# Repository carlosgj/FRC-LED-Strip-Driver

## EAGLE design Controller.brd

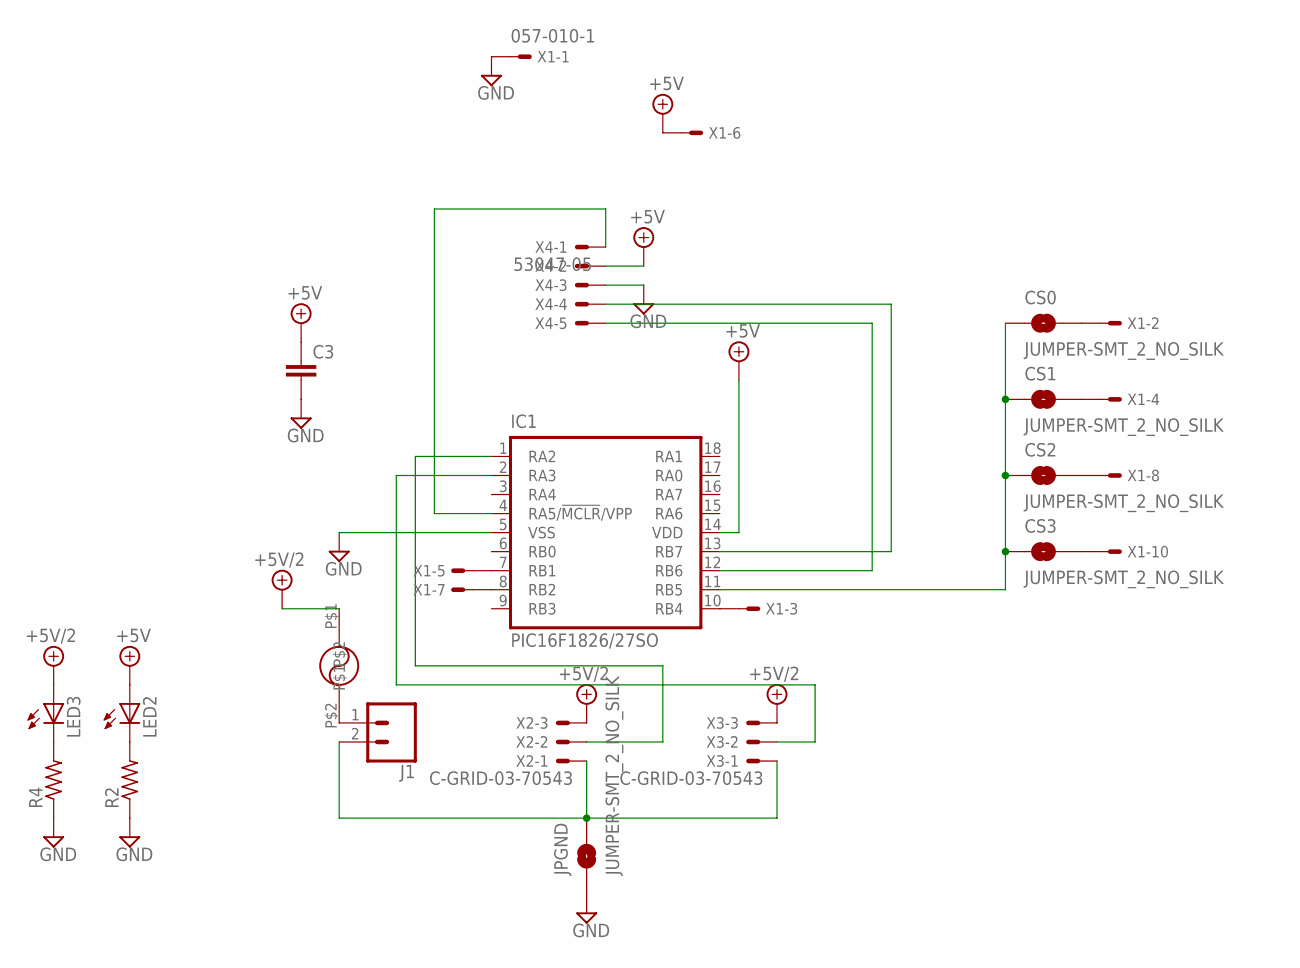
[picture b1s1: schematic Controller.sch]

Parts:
C3: C-EUC1206; C1206
CS0, CS1, CS2, CS3: JUMPER-SMT_2_NO_SILK; SMT-JUMPER_2_NO_SILK
IC1: PIC16F1826/27SO; SO-18W
J1: CONN_023.5MM; SCREWTERMINAL-3.5MM-2
JPGND: JUMPER-SMT_2_NO_SILK; SMT-JUMPER_2_NO_SILK
LED2, LED3: LEDCHIPLED_1206; CHIPLED_1206
R2, R4: R-US_R1206; R1206
U$3: 0034.6081; MSF250
X1: 057-010-1
X2, X3: C-GRID-03-70543; 70543-03
X4: 53047-05

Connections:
+5V: C3.1, IC1.14 (VDD), LED2.A, X1.6, X4.2
+5V/2: LED3.A, U$3.P$1, X2.3, X3.3
GND: C3.2, IC1.5 (VSS), JPGND.1, R2.1, R4.1, X1.1, X4.3
unnamed: IC1.10 (RB4), X1.3
unnamed: IC1.7 (RB1), X1.5
unnamed: IC1.8 (RB2), X1.7
unnamed: CS0.1, CS1.1, CS2.1, CS3.1, IC1.11 (RB5)
unnamed: CS0.2, X1.2
unnamed: CS1.2, X1.4
unnamed: CS2.2, X1.8
unnamed: CS3.2, X1.10
unnamed: J1.1, U$3.P$2
unnamed: LED3.C, R4.2
unnamed: J1.2, JPGND.2, X2.1, X3.1
unnamed: IC1.1 (RA2), X2.2
unnamed: IC1.2 (RA3), X3.2
unnamed: IC1.4 (RA5/!MCLR!/VPP), X4.1
unnamed: IC1.13 (RB7), X4.4
unnamed: IC1.12 (RB6), X4.5
unnamed: LED2.C, R2.2

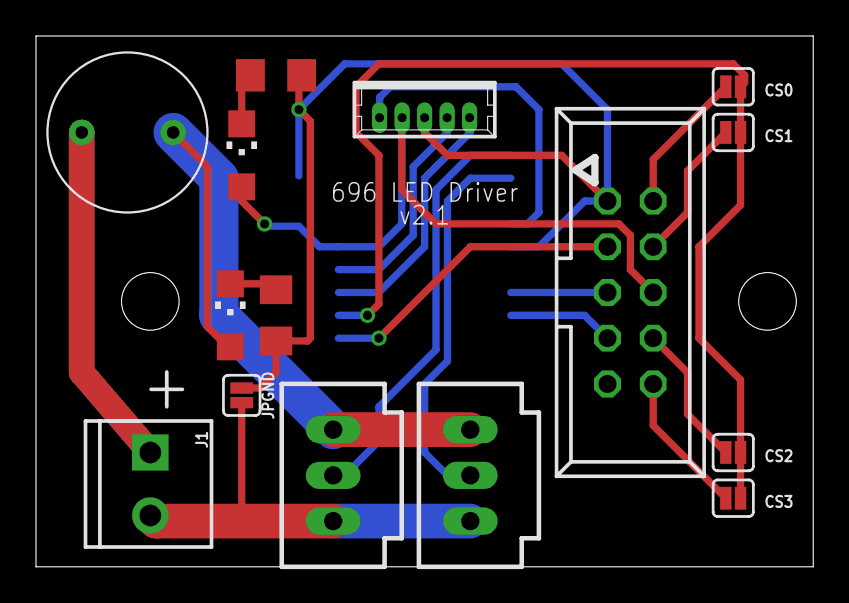
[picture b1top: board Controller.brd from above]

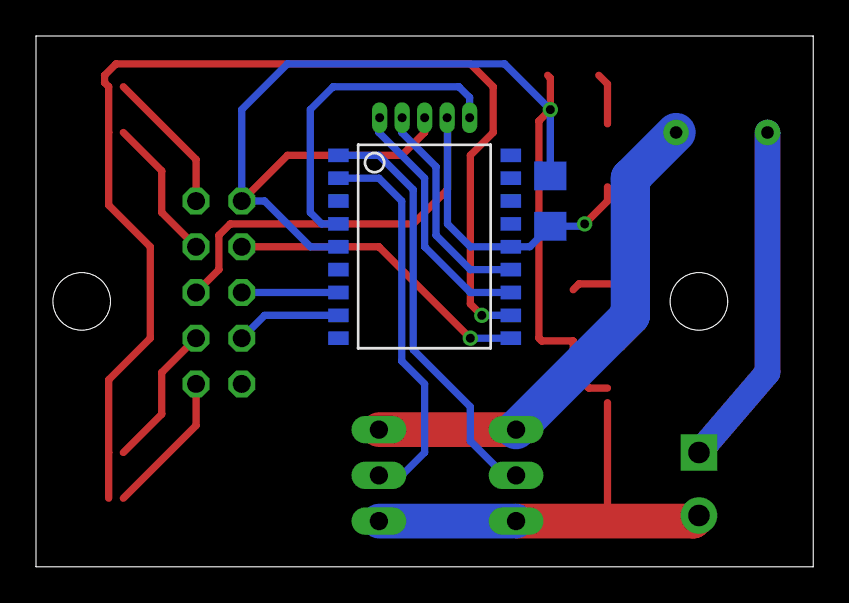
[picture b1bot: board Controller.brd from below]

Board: 2 copper layers, 43.2 x 29.5 mm, 17 parts (2 on the bottom side), 20 nets.

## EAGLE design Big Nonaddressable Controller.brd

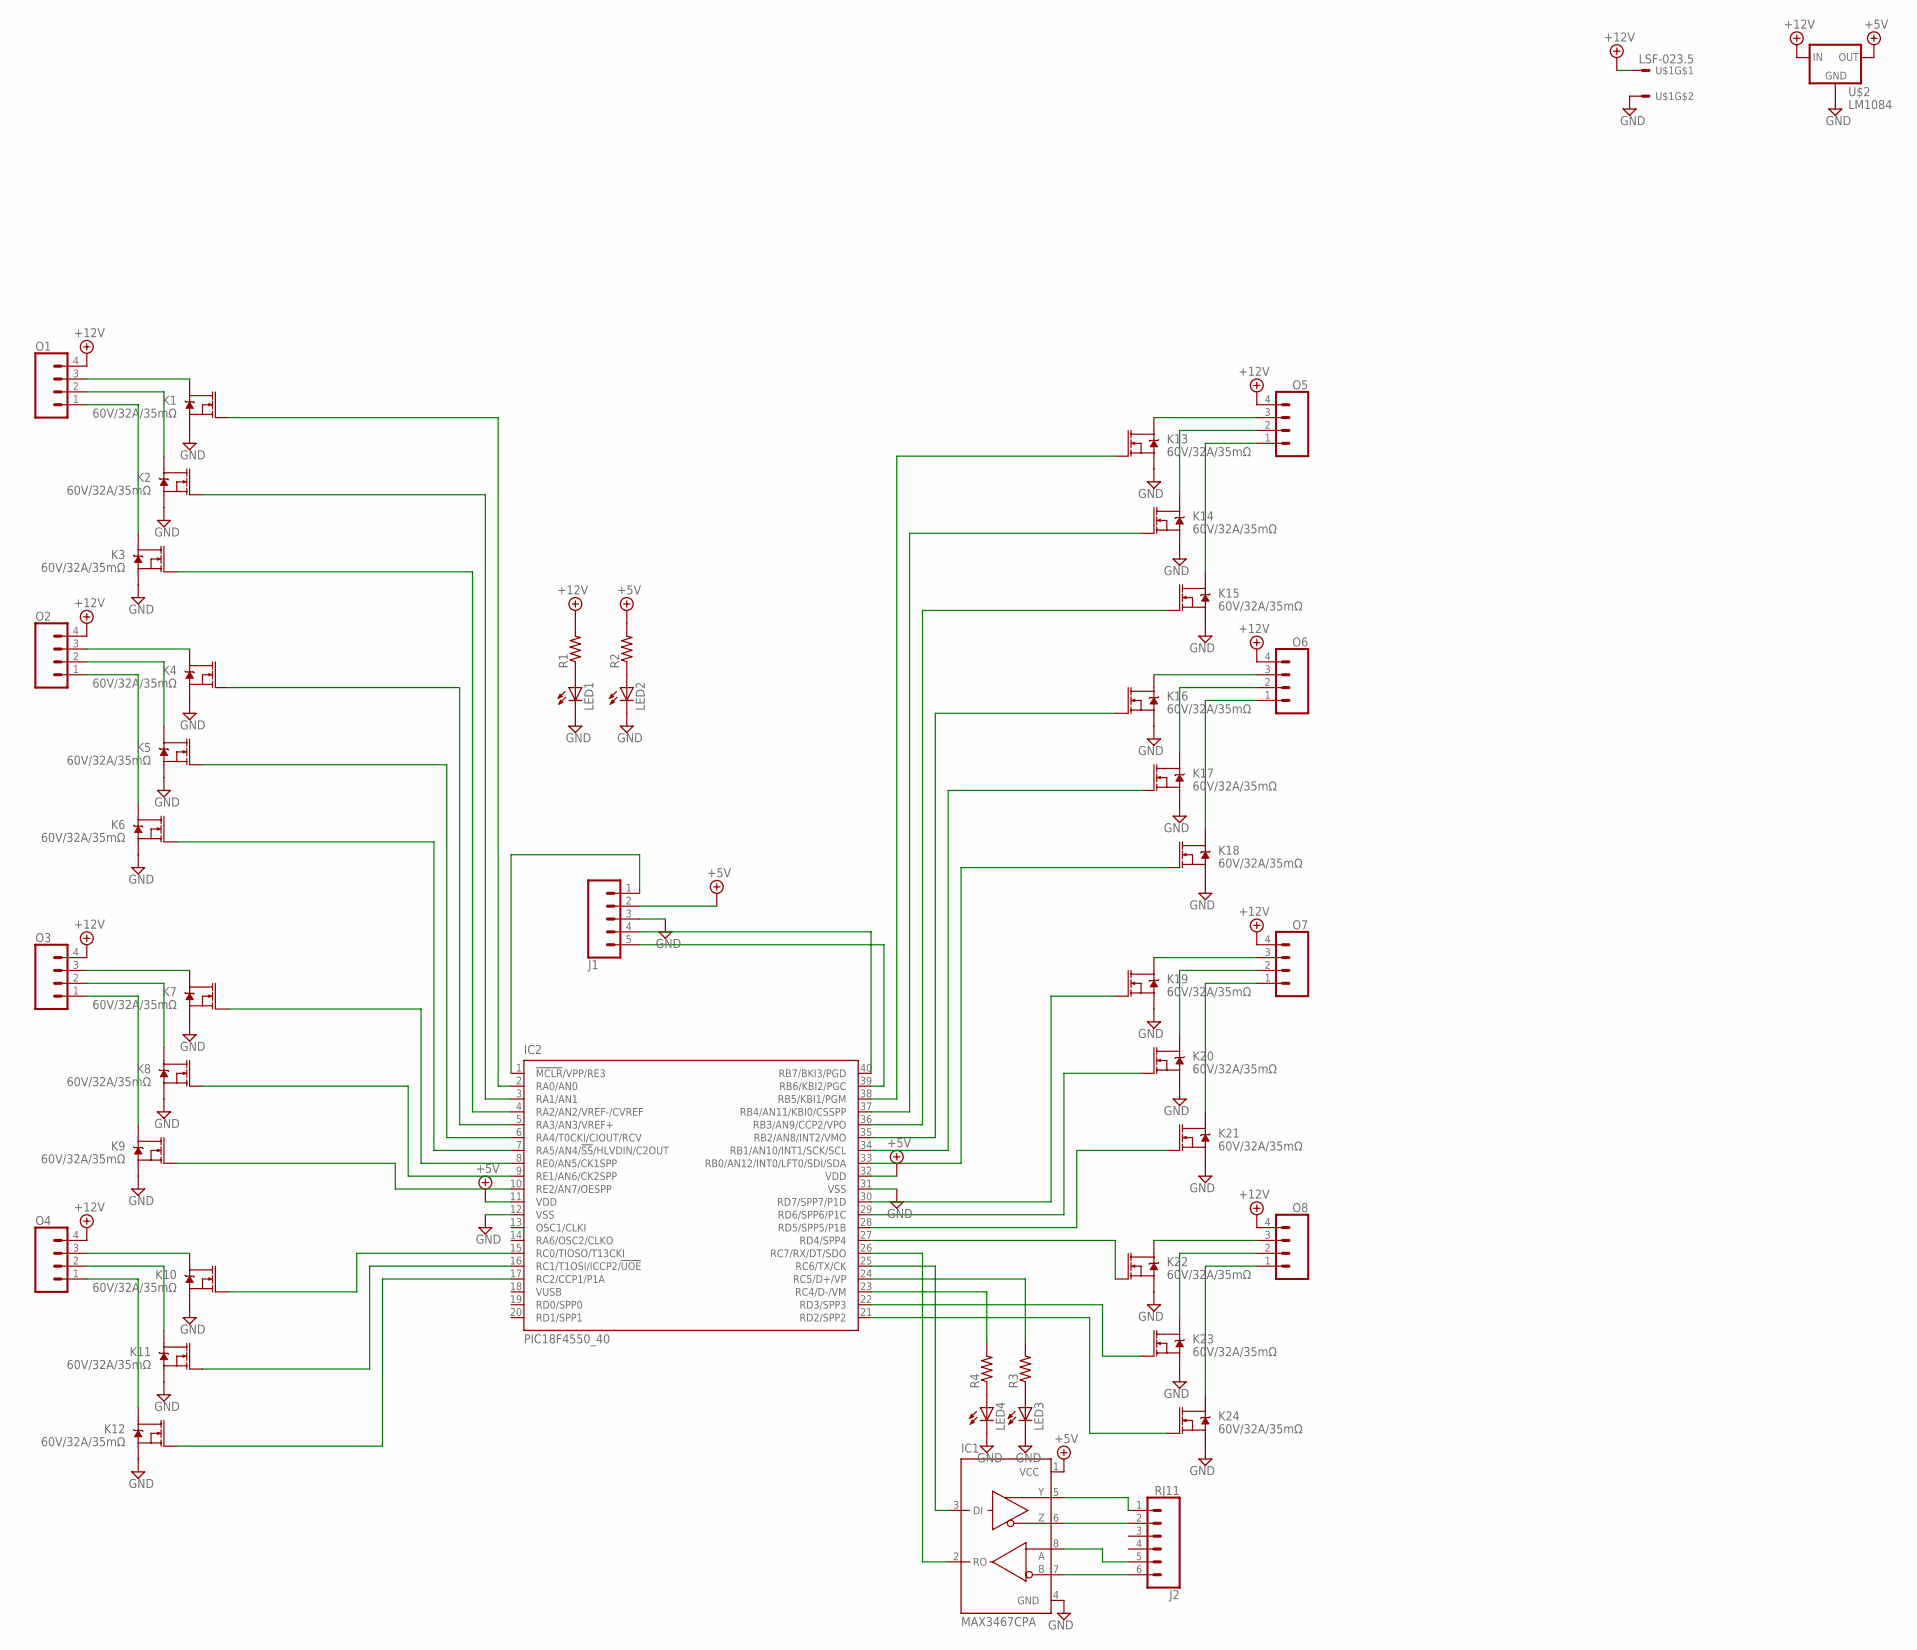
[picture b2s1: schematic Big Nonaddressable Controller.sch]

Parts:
IC1: MAX3467CPA; SO08
IC2: PIC18F4550_40; DIL40
J1: CONN_05; 1X05
J2: RJ11; RJ11-6
K1, K2, K3, K4, K5, K6, K7, K8, K9, K10, K11, K12, K13, K14, K15, K16, K17, K18, K19, K20, K21, K22, K23, K24: 60V/32A/35mΩ; TO220V
LED1, LED2, LED3, LED4: LED3MM
O1, O2, O3, O4, O5, O6, O7, O8: CONN_04; 1X04
R1, R2, R3, R4: R-US_0204/2V; 0204V
U$1: LSF-023.5; LSF-3.5
U$2: LM1084; D2PACK

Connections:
+5V: IC1.1 (VCC), IC2.11 (VDD), IC2.32 (VDD), J1.2, R2.2, U$2.2 (OUT)
+12V: O1.4, O2.4, O3.4, O4.4, O5.4, O6.4, O7.4, O8.4, R1.2, U$1.P$3, U$2.3 (IN)
GND: IC1.4 (GND), IC2.12 (VSS), IC2.31 (VSS), J1.3, K1.3 (S), K2.3 (S), K3.3 (S), K4.3 (S), K5.3 (S), K6.3 (S), K7.3 (S), K8.3 (S), K9.3 (S), K10.3 (S), K11.3 (S), K12.3 (S), K13.3 (S), K14.3 (S), K15.3 (S), K16.3 (S), K17.3 (S), K18.3 (S), K19.3 (S), K20.3 (S), K21.3 (S), K22.3 (S), K23.3 (S), K24.3 (S), LED1.K (C), LED2.K (C), LED3.K (C), LED4.K (C), U$1.P$4, U$2.1 (GND)
unnamed: IC2.40 (RB7/BKI3/PGD), J1.4
unnamed: IC2.39 (RB6/KBI2/PGC), J1.5
unnamed: IC1.2 (RO), IC2.26 (RC7/RX/DT/SDO)
unnamed: IC1.3 (DI), IC2.25 (RC6/TX/CK)
unnamed: K4.2 (D), O2.3
unnamed: K5.2 (D), O2.2
unnamed: K6.2 (D), O2.1
unnamed: IC2.2 (RA0/AN0), K1.1 (G)
unnamed: IC2.3 (RA1/AN1), K2.1 (G)
unnamed: IC2.4 (RA2/AN2/VREF-/CVREF), K3.1 (G)
unnamed: IC2.1 (!MCLR!/VPP/RE3), J1.1
unnamed: IC2.5 (RA3/AN3/VREF+), K4.1 (G)
unnamed: IC2.6 (RA4/T0CKI/CIOUT/RCV), K5.1 (G)
unnamed: IC2.7 (RA5/AN4/!SS!/HLVDIN/C2OUT), K6.1 (G)
unnamed: K7.2 (D), O3.3
unnamed: K8.2 (D), O3.2
unnamed: K9.2 (D), O3.1
unnamed: K10.2 (D), O4.3
unnamed: K11.2 (D), O4.2
unnamed: K12.2 (D), O4.1
unnamed: IC2.8 (RE0/AN5/CK1SPP), K7.1 (G)
unnamed: IC2.9 (RE1/AN6/CK2SPP), K8.1 (G)
unnamed: K1.2 (D), O1.3
unnamed: K2.2 (D), O1.2
unnamed: K3.2 (D), O1.1
unnamed: IC2.10 (RE2/AN7/OESPP), K9.1 (G)
unnamed: IC2.17 (RC2/CCP1/P1A), K12.1 (G)
unnamed: IC2.16 (RC1/T1OSI/ICCP2/!UOE), K11.1 (G)
unnamed: IC2.15 (RC0/TIOSO/T13CKI), K10.1 (G)
unnamed: K13.2 (D), O5.3
unnamed: K14.2 (D), O5.2
unnamed: K15.2 (D), O5.1
unnamed: IC2.38 (RB5/KBI1/PGM), K13.1 (G)
unnamed: IC2.37 (RB4/AN11/KBI0/CSSPP), K14.1 (G)
unnamed: IC2.36 (RB3/AN9/CCP2/VPO), K15.1 (G)
unnamed: K16.2 (D), O6.3
unnamed: K17.2 (D), O6.2
unnamed: K18.2 (D), O6.1
unnamed: IC2.35 (RB2/AN8/INT2/VMO), K16.1 (G)
unnamed: IC2.34 (RB1/AN10/INT1/SCK/SCL), K17.1 (G)
unnamed: IC2.33 (RB0/AN12/INT0/LFT0/SDI/SDA), K18.1 (G)
unnamed: K19.2 (D), O7.3
unnamed: K20.2 (D), O7.2
unnamed: K21.2 (D), O7.1
unnamed: K22.2 (D), O8.3
unnamed: K23.2 (D), O8.2
unnamed: K24.2 (D), O8.1
unnamed: IC2.30 (RD7/SPP7/P1D), K19.1 (G)
unnamed: IC2.29 (RD6/SPP6/P1C), K20.1 (G)
unnamed: IC2.28 (RD5/SPP5/P1B), K21.1 (G)
unnamed: IC2.27 (RD4/SPP4), K22.1 (G)
unnamed: IC2.22 (RD3/SPP3), K23.1 (G)
unnamed: IC2.21 (RD2/SPP2), K24.1 (G)
unnamed: IC1.7 (B), J2.6
unnamed: IC1.8 (A), J2.5
unnamed: IC1.5 (Y), J2.1
unnamed: IC1.6 (Z), J2.2
unnamed: LED1.A, R1.1
unnamed: LED2.A, R2.1
unnamed: LED3.A, R3.1
unnamed: LED4.A, R4.1
unnamed: IC2.24 (RC5/D+/VP), R3.2
unnamed: IC2.23 (RC4/D-/VM), R4.2

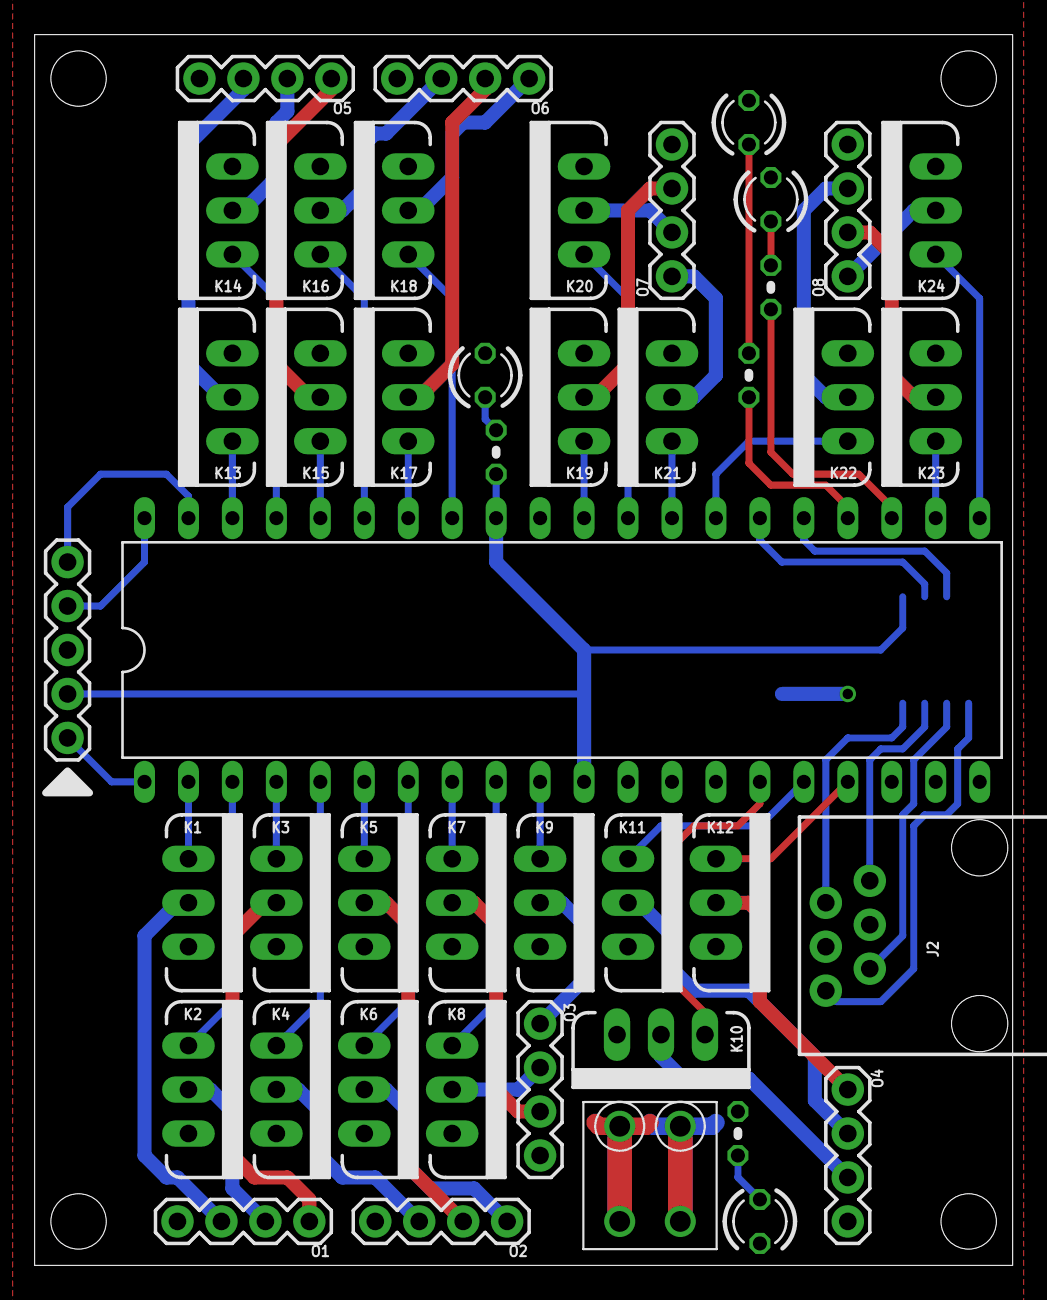
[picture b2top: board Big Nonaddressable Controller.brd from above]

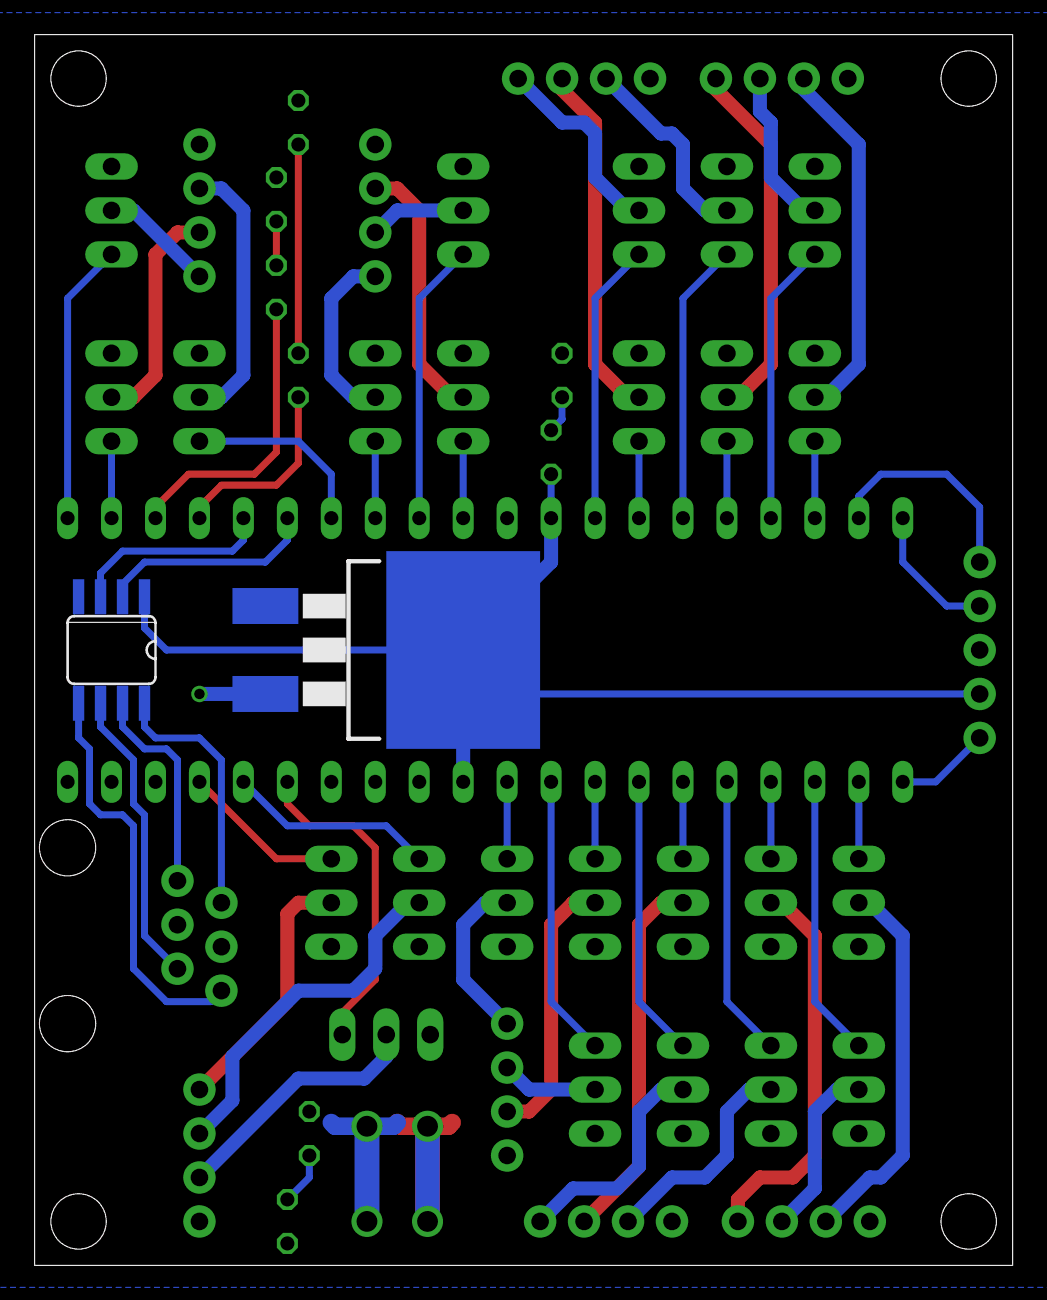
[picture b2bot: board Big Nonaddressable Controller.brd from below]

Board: 2 copper layers, 56.5 x 71.1 mm, 46 parts (2 on the bottom side), 66 nets.

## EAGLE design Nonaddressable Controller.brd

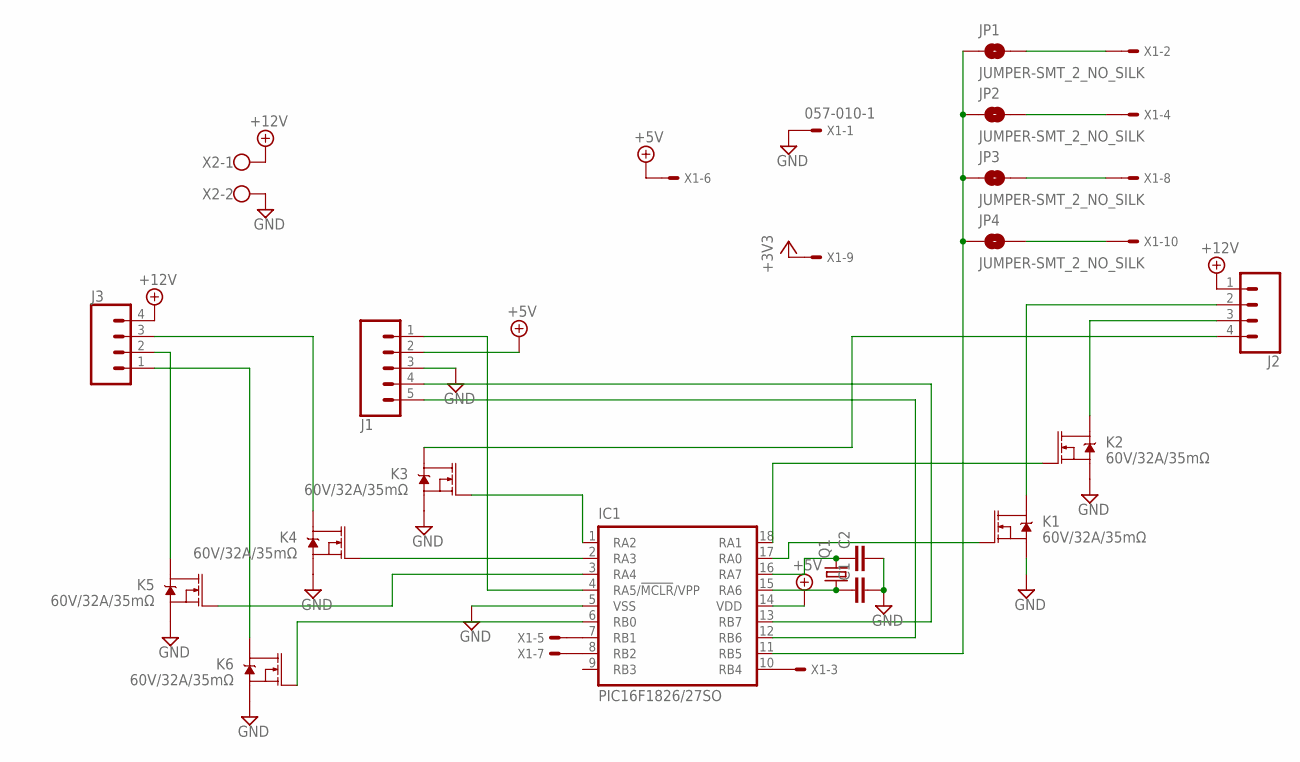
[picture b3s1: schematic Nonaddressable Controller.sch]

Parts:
C1, C2: C-EUC1206; C1206
IC1: PIC16F1826/27SO; SO-18W
J1: CONN_05; 1X05
J2, J3: CONN_04; 1X04
JP1, JP2, JP3, JP4: JUMPER-SMT_2_NO_SILK; SMT-JUMPER_2_NO_SILK
K1, K2, K3, K4, K5, K6: 60V/32A/35mΩ; TO220V
Q1: CRYSTALHC49S; HC49/S
X1: 057-010-1
X2: W237-102

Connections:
+3V3: X1.9
+5V: IC1.14 (VDD), J1.2, X1.6
+12V: J2.1, J3.4, X2.1
GND: C1.2, C2.2, IC1.5 (VSS), J1.3, K1.3 (S), K2.3 (S), K3.3 (S), K4.3 (S), K5.3 (S), K6.3 (S), X1.1, X2.2
unnamed: IC1.10 (RB4), X1.3
unnamed: IC1.7 (RB1), X1.5
unnamed: IC1.8 (RB2), X1.7
unnamed: JP1.2, X1.2
unnamed: JP2.2, X1.4
unnamed: JP3.2, X1.8
unnamed: JP4.2, X1.10
unnamed: IC1.11 (RB5), JP1.1, JP2.1, JP3.1, JP4.1
unnamed: C1.1, IC1.15 (RA6), Q1.1
unnamed: C2.1, IC1.16 (RA7), Q1.2
unnamed: IC1.4 (RA5/!MCLR!/VPP), J1.1
unnamed: IC1.13 (RB7), J1.4
unnamed: IC1.12 (RB6), J1.5
unnamed: IC1.17 (RA0), K1.1 (G)
unnamed: IC1.18 (RA1), K2.1 (G)
unnamed: IC1.1 (RA2), K3.1 (G)
unnamed: IC1.2 (RA3), K4.1 (G)
unnamed: IC1.3 (RA4), K5.1 (G)
unnamed: IC1.6 (RB0), K6.1 (G)
unnamed: J2.2, K1.2 (D)
unnamed: J2.3, K2.2 (D)
unnamed: J2.4, K3.2 (D)
unnamed: J3.3, K4.2 (D)
unnamed: J3.2, K5.2 (D)
unnamed: J3.1, K6.2 (D)

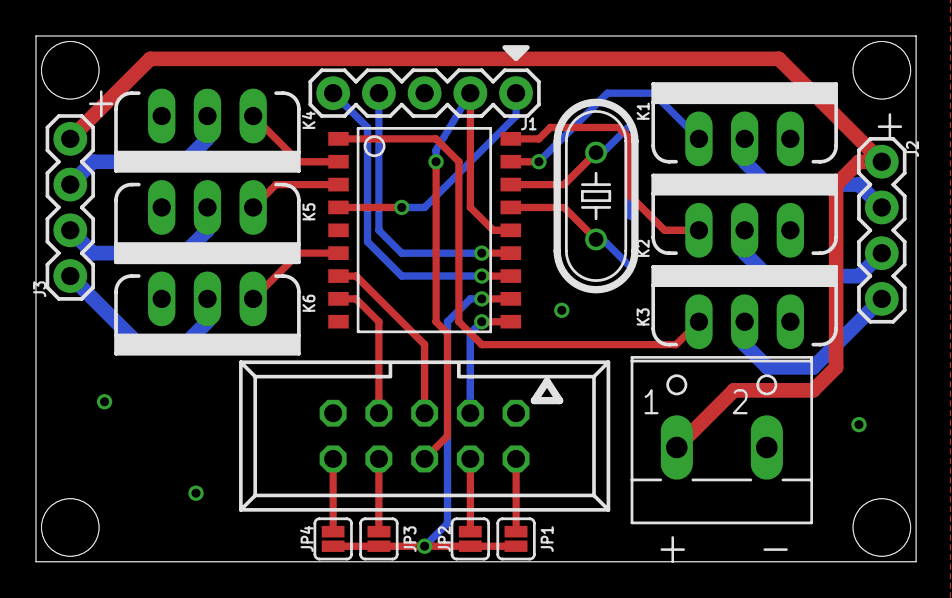
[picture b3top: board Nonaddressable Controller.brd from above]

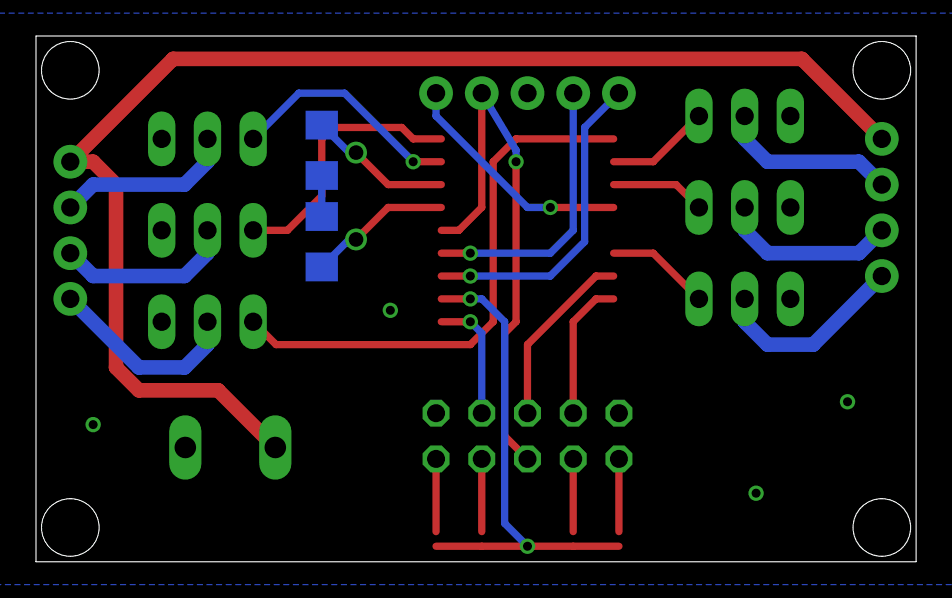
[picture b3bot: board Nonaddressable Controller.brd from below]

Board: 2 copper layers, 48.9 x 29.2 mm, 19 parts (2 on the bottom side), 28 nets.

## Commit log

2018-01-15 Code
2018-01-20 Added plain LED strip driver
2018-01-31 Work on code for nonaddressable strip controller
2018-01-31 Should work
2018-02-05 Rainbow mode works
2018-03-16 Green heartbeat
2018-03-16 Added many patterns
2018-03-16 Added pattern spreadsheet
2018-03-17 Use of crystal is buggy currently
2018-03-30 Got SPI working
2018-03-30 Arduino SPI sender
2018-09-01 no message
2019-01-30 Updated design to include 5V power supply
2019-02-04 Basic LED strip control works
2019-02-05 Important tweaks to HSV-to-RGB algorithm
2019-02-07 Implementing SPI communication
2019-02-24 Adding new patterns
2019-10-08 Implementing patterns
2019-10-08 Removing onboard voltage regulator
2019-10-08 Implementing more patterns
2019-10-09 Minor adjustments to "slow" and "fast"
2019-10-09 Arduino SPI test code works with addressable controller
2019-10-10 Update to 16f1827 profile

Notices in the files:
parts and their libraries:
SparkFun-Connectors: Licensing: Creative Commons ShareAlike 4.0 International - https://creativecommons.org/licenses/by-sa/4.0
